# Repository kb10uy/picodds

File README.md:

# PicoDDS

RP2040 (Seeed XIAO RP2040) と MCP4922 を利用した簡易ファンクションジェネレーター

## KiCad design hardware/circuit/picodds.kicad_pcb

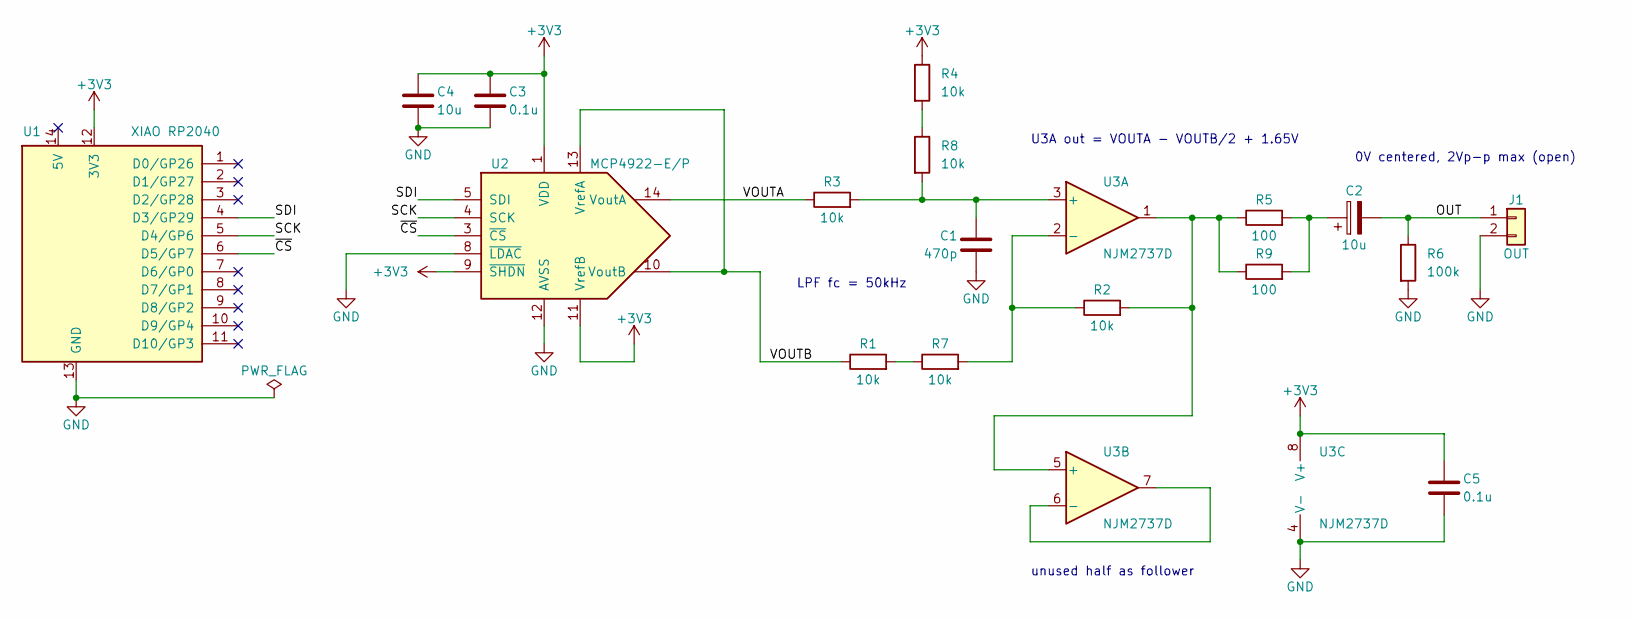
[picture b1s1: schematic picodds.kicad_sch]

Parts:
C1: 470p; C_Disc_D3.0mm_W1.6mm_P2.50mm
C2: 10u; CP_Radial_D5.0mm_P2.50mm
C3, C5: 0.1u; C_Disc_D3.0mm_W1.6mm_P2.50mm
C4: 10u; C_Disc_D5.0mm_W2.5mm_P2.50mm
J1: OUT; PinHeader_1x02_P2.54mm_Vertical
R1, R2, R3, R4, R7, R8: 10k; R_Axial_DIN0207_L6.3mm_D2.5mm_P7.62mm_Horizontal
R5, R9: 100; R_Axial_DIN0207_L6.3mm_D2.5mm_P7.62mm_Horizontal
R6: 100k; R_Axial_DIN0207_L6.3mm_D2.5mm_P7.62mm_Horizontal
U1: XIAO RP2040; XIAO_RP2040_THT
U2: MCP4922-E/P; DIP-14_W7.62mm
U3: NJM2737D; DIP-8_W7.62mm

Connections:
+3V3: C3.1, C4.1, C5.1, R4.1, U1.12 (3V3), U2.1 (VDD), U2.9 (~SHDN), U2.11 (VrefB), U3.8 (V+)
/OUT: C2.2, J1.1, R6.1
/SCK: U1.5 (D4/GP6), U2.4 (SCK)
/SDI: U1.4 (D3/GP29), U2.5 (SDI)
/VOUTA: R3.1, U2.14 (VoutA)
/VOUTB: R1.1, U2.10 (VoutB), U2.13 (VrefA)
/~CS: U1.6 (D5/GP7), U2.3 (~CS)
GND: C1.2, C3.2, C4.2, C5.2, J1.2, R6.2, U1.13 (GND), U2.8 (~LDAC), U2.12 (AVSS), U3.4 (V-)
unnamed: C2.1, R5.2, R9.2
unnamed: R1.2, R7.1
unnamed: R4.2, R8.1
unnamed: C1.1, R3.2, R8.2, U3.3 (+)
unnamed: R2.1, R7.2, U3.2 (-)
unnamed: R2.2, R5.1, R9.1, U3.1, U3.5 (+)
unnamed: U3.6 (-), U3.7

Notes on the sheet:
LPF fc = 50kHz
U3A out = VOUTA - VOUTB/2 + 1.65V
0V centered, 2Vp-p max (open)
unused half as follower

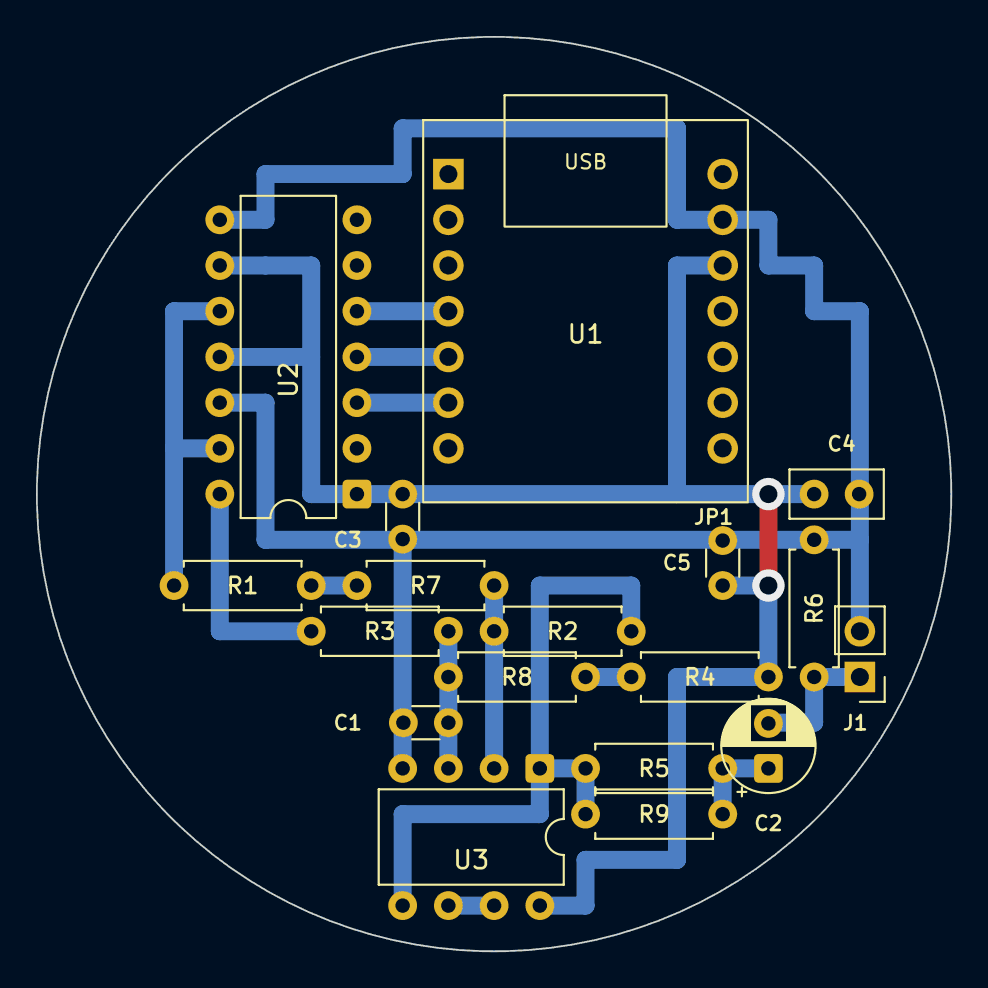
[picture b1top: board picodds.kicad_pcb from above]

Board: 2 copper layers, 50.8 x 50.8 mm, 18 parts (0 on the bottom side), 15 nets.
